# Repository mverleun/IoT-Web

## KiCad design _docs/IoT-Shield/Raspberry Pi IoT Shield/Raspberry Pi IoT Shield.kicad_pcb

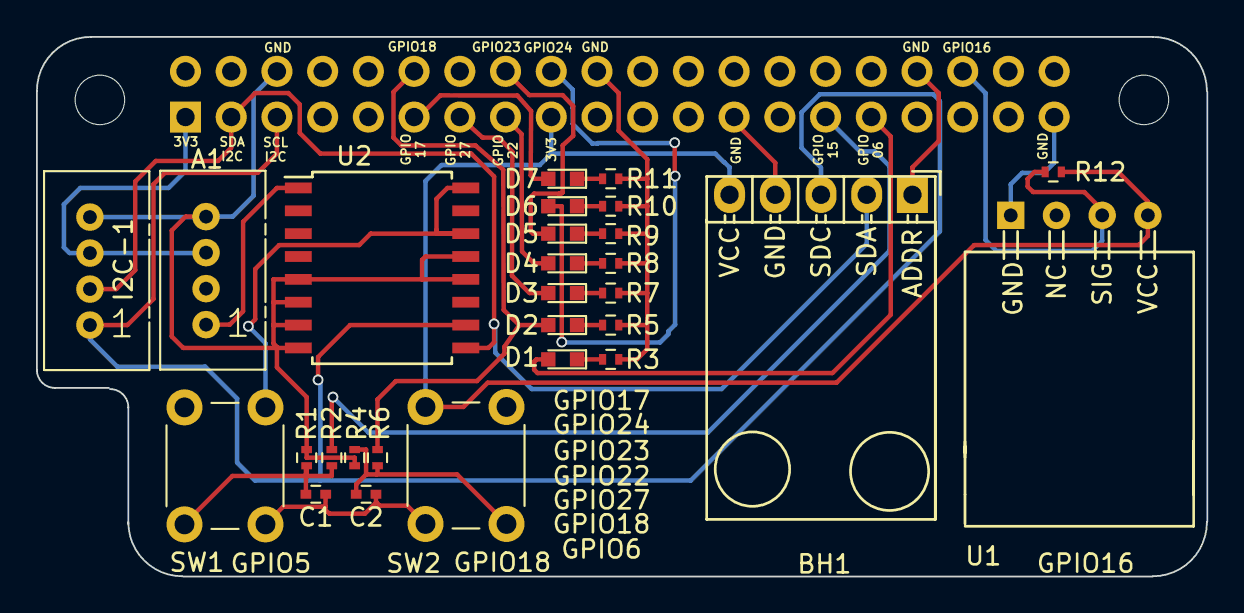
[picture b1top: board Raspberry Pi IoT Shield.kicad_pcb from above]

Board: 2 copper layers, 65.0 x 30.0 mm, 29 parts (0 on the bottom side), 24 nets.

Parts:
A1: JST-PH-2.0; Grove_1x04
BH1: BH1750 (GY-302); Pin_Header_Angled_1x05
C1, C2: 47nF; C_0402
D1: LED 6 Yellow; LED_0603
D2: LED 18 Red; LED_0603
D3: LED 27 Red; LED_0603
D4: LED 22 Red; LED_0603
D5: LED 23 Red; LED_0603
D6: LED 24 Red; LED_0603
D7: LED 17 Green; LED_0603
I2C-1: JST-PH-2.0; Grove_1x04
J1: RPi_GPIO; Pin_Header_Straight_2x20
R1, R4: 10K; R_0402
R2, R6: 1K; R_0402
R3, R5, R7, R8, R9, R10, R11: 470; R_0402
R12: 4K7; R_0402
SW1, SW2: SW_Push: JT 0102; SW_PUSH_6mm_h9.5mm
U1: DHT11
U2: PCF8591T; SOIC-16W_7.5x10.3mm_Pitch1.27mm

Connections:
+3V3: A1.3, BH1.5, C1.1, C2.1, I2C-1.3, J1.1, J1.17, R12.1, SW1.1, SW2.1, U1.4, U2.14, U2.16
+5V: J1.2, J1.4
GNDA: A1.4, BH1.1, BH1.4, I2C-1.4, J1.6, J1.9, J1.14, J1.20, J1.25, J1.30, J1.34, J1.39, R1.2, R3.2, R4.2, R5.2, R7.2, R8.2, R9.2, R10.2, R11.2, U1.1, U2.5, U2.6, U2.7, U2.8, U2.12, U2.13
GPIO02-SDA1-I2C: BH1.2, I2C-1.2, J1.3, U2.9
GPIO03-SCL1-I2C: BH1.3, I2C-1.1, J1.5, U2.10
GPIO5: J1.29, R2.1
GPIO6: D1.2, J1.31
GPIO16: J1.36, R12.2, U1.3
GPIO17: D7.2, J1.11
GPIO18: D2.2, J1.12, R6.1
GPIO22: D4.2, J1.15
GPIO23: D5.2, J1.16
GPIO24: D6.2, J1.18
GPIO27: D3.2, J1.13
unnamed: A1.1, U2.1
unnamed: C1.2, R1.1, R2.2, SW1.2
unnamed: C2.2, R4.1, R6.2, SW2.2
unnamed: D1.1, R3.1
unnamed: D2.1, R5.1
unnamed: D3.1, R7.1
unnamed: D4.1, R8.1
unnamed: D5.1, R9.1
unnamed: D6.1, R10.1
unnamed: D7.1, R11.1

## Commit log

2018-05-24 Uploaded web to Github
2018-05-24 Updated website
2018-05-24 Added installation instructions
2018-05-24 Updated Node RED documentation
2018-05-24 Update documentation Node RED
2018-05-24 Added documentation Wemos D1 mini
2018-05-25 Chapter on firmwares
2018-05-25 Updated firmware documentation
2018-05-25 Corrected typo's
2018-05-25 Test remote include
2018-05-25 Included firmware README's from Github
2018-05-25 Fixed typo
2018-05-25 Removed leftovers
2018-05-25 Added some info about README.md
2018-05-25 Changed _config.yml
2018-05-25 Modified _config.yml
2018-05-26 Fixed image
2018-05-26 Added documentation homie
2018-05-26 Updated homie.md
2018-05-26 Fixed typo's
2018-05-26 Changed title
2018-05-26 Fixes
2018-05-27 Link to releases
2018-05-27 Included download links
2018-05-27 Changed footer
2018-05-27 Owntracks
2018-06-04 Added post
2018-06-04 Post
2018-06-05 Added RPI Shield
2018-06-05 Add blog
2018-06-05 Added blog
2018-06-08 Added info
2018-06-08 Added picture
2018-06-08 Extended names of firmwares
2018-06-09 Added overview
2018-06-11 Cleanedup image
2018-06-11 Added learning objectives
2018-06-11 Fixed URL
2018-06-11 Changed layout
2018-06-12 Test
2018-06-12 Changed bootwatch
2018-06-12 Added schematics
2018-06-12 Updated learning objectives
2018-06-12 Moved files to correct repo
2018-06-12 Added english CC License
2018-06-12 Updated footer
2018-06-12 Blog post
2018-06-12 Blog
2018-06-22 Changed formatting of I2C
2018-06-22 Exclude .DS_Store
2018-09-04 Added ESP Homelib
2018-09-04 Added ESPHomelib
2018-09-04 Wrong title
2018-09-04 Typo
2018-09-04 Changed the format into two solutions for two platforms
2018-09-04 Entered correct platform information
2018-09-04 Added I2C section
2018-09-08 Location of files has changed
2019-04-26 Added submodule Wow
2019-04-26 Relocated submodules
2019-04-26 Added Demo
2019-04-26 Removed corrupt file
2019-04-27 Change docs to contain permalink info
2019-04-27 Fixed links
2019-04-27 update documents
2019-05-19 Add lessons
2019-05-19 Changed name of ESPHomelib into ESPHome
2019-05-19 Moved files around
2019-05-19 Started lesson
2019-05-20 Updated lesson 1
2019-05-20 Added images
2019-05-20 Lesson 2
2019-05-20 Added lesson 3
2019-05-20 Lesson 3
2019-05-20 Update lesson 3
2019-05-20 Lesson 4
2019-05-20 Github security warnings fixed
2019-05-21 Added lesson 5
2019-05-30 Changed document structure
2019-05-30 Add installation guides
2019-06-02 Updated .gitignore
2019-10-31 Bump jekyll from 3.4.3 to 3.6.3
    Bumps [jekyll](https://github.com/jekyll/jekyll) from 3.4.3 to 3.6.3.
    - [Release notes](https://github.com/jekyll/jekyll/releases)
    - [Changelog](https://github.com/jekyll/jekyll/blob/master/History.markdown)
    - [Commits](https://github.com/jekyll/jekyll/compare/v3.4.3...v3.6.3)

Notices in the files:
_docs/IoT-Shield/Raspberry Pi IoT Shield/Raspberry Pi IoT Shield.kicad_pcb:
License: CC BY-NC-SA 4.0
